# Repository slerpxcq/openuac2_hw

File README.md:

# openuac2_hw
Hardware platform for OpenUAC2 project

**WARNING**: The form factor of this module is compatible with combo384, however, the pinout is **NOT** fully the same. Check carefully before installing this card to any existing system.

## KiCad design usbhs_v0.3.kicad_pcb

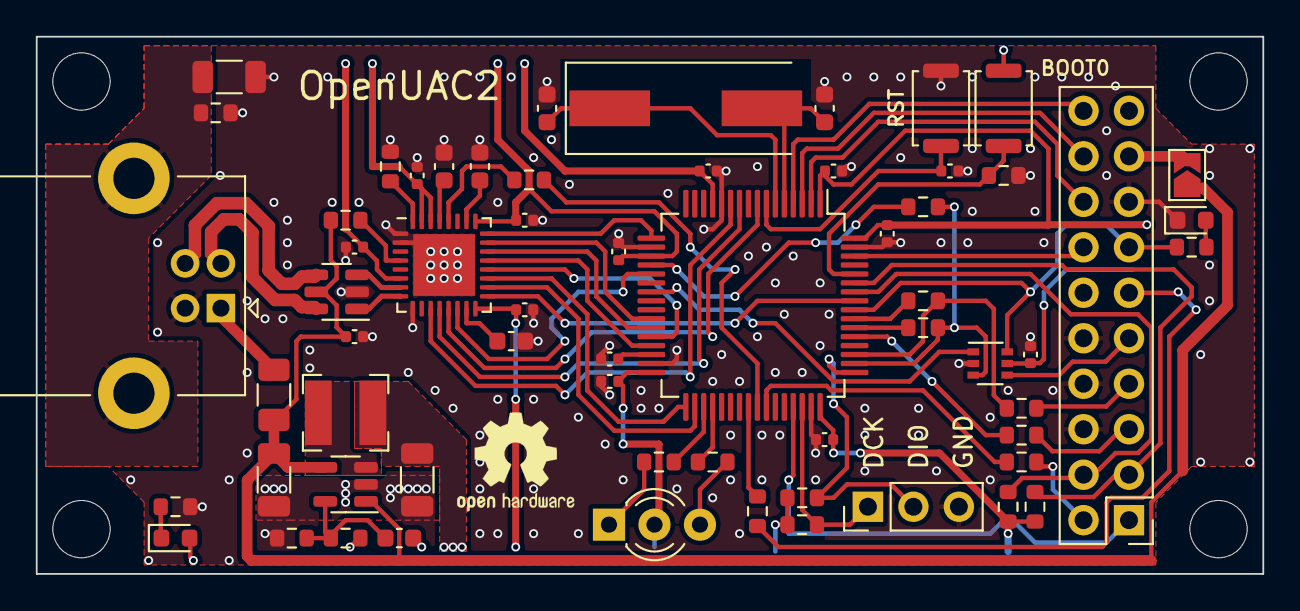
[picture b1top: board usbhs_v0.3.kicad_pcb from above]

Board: 2 copper layers, 68.5 x 30.0 mm, 66 parts (0 on the bottom side), 66 nets.

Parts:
C1, C2, C3, C4, C5, C6, C10, C12, C15, C16, C17, C18, C19, C23: 104; C_0402_1005Metric
C7, C8: 106; C_1206_3216Metric
C9: 22p; C_0603_1608Metric
C11: 104/50V; C_1206_3216Metric
C13, C14: 33p; C_0603_1608Metric
C20, C21, C22: 475; C_0603_1608Metric
D1: LED_Dual_KAK; LED_D3.0mm-3
D2: LED_WHITE; LED_0603_1608Metric
D3: LED_YELLOW; LED_0603_1608Metric
F1: 500mA; Fuse_1206_3216Metric
H1, H2, H3, H4: MountingHole; MountingHole_3.2mm_M3
J1: USB_B; USB_B_Lumberg_2411_02_Horizontal
J2: Conn_01x03; PinHeader_1x03_P2.54mm_Vertical
J3: Conn_02x10_Odd_Even; PinHeader_2x10_P2.54mm_Vertical
JP1: SolderJumper_2_Open; SolderJumper-2_P1.3mm_Open_TrianglePad1.0x1.5mm
L1: 4.7u; L_Bourns-SRN4018
R1, R2, R7, R21: 1k; R_0603_1608Metric
R3: 680k; R_0603_1608Metric
R4: 150k; R_0603_1608Metric
R5, R11, R13: 0; R_0603_1608Metric
R6: 1M; R_0603_1608Metric
R8, R9, R17: 10; R_0603_1608Metric
R10, R12, R19: 10k; R_0603_1608Metric
R14: 100k; R_0603_1608Metric
R15, R16: 4.7k; R_0603_1608Metric
R18, R20: 22; R_0603_1608Metric
R22: 12k; R_0603_1608Metric
SW1, SW2: SW_Push; SW_Push_SPST_NO_Alps_SKRK
U1: SY8088; SOT-23-5
U2: USBLC6-2SC6; SOT-23-6
U3: STM32F446RETx; LQFP-64_10x10mm_P0.5mm
U4: USB3300-EZK; QFN-32-1EP_5x5mm_P0.5mm_EP3.45x3.45mm
U5: 74LVC1G3157; SOT-363_SC-70-6
Y1: 12.288M; Crystal_SMD_HC49-SD

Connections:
+3V3: C1.2, C2.2, C3.2, C4.2, C5.2, C6.2, C7.2, C9.1, C15.1, C16.1, C17.1, C18.1, C23.1, D1.2 (A), D2.2 (A), J3.19, L1.2, R3.1, R10.1, R12.1, R15.1, R16.1, SW1.2, U3.1 (VBAT), U3.13 (VDDA), U3.19 (VDD), U3.32 (VDD), U3.48 (VDD), U3.64 (VDD), U4.6 (VDD3.3), U4.16 (VDD3.3), U4.25 (VDD3.3), U4.30 (VDD3.3), U4.31 (REG_EN), U5.5 (VCC)
/24M_CK: R8.2, U4.28 (XI)
/BOOT0: R14.2, SW1.1, U3.60 (BOOT0)
/DSDOE: J3.13, R21.2, U3.56 (PB4), U5.6
/EXTI2: R11.1, U3.54 (PD2)
/F0: J3.14, U3.62 (PB9)
/F1: J3.16, U3.2 (PC13)
/F2: J3.18, U3.3 (PC14)
/F3: J3.20, U3.4 (PC15)
/I2C1_SCL: J3.4, R15.2, U3.58 (PB6)
/I2C1_SDA: J3.3, R16.2, U3.59 (PB7)
/I2S1_CK: R13.2, U3.55 (PB3)
/I2S1_SD: U3.23 (PA7), U5.1
/I2S1_WS: R5.1, U3.20 (PA4)
/I2S3_CK: R13.1, R18.1, U3.51 (PC10)
/I2S3_SD: R20.1, U3.53 (PC12)
/I2S3_WS: R5.2, R11.2, U3.50 (PA15), U5.3
/I2S_BCK/DSDCK: J3.7, R18.2
/I2S_DATA/DSD1: J3.5, R20.2
/I2S_LRCK/DSD2: J3.9, U5.4
/I2S_MCK: J3.11, R17.2
/LED1: R1.2, U3.35 (PB14)
/LED2: R2.2, U3.36 (PB15)
/NRST: C19.1, SW2.2, U3.7 (NRST)
/PDN: J3.1, U3.45 (PA12)
/RCC_MCO1: R8.1, U3.41 (PA8)
/RCC_MCO2: R17.1, U3.40 (PC9)
/SPDIF_TX: J3.2, R9.2
/SWD_CK: J2.2, R12.2, U3.49 (PA14)
/SWD_IO: J2.1, R10.2, U3.46 (PA13)
/ULPI_CK: U3.21 (PA5), U4.14 (CLKOUT)
/ULPI_D0: U3.17 (PA3), U4.24 (DATA0)
/ULPI_D1: U3.26 (PB0), U4.23 (DATA1)
/ULPI_D2: U3.27 (PB1), U4.22 (DATA2)
/ULPI_D3: U3.29 (PB10), U4.21 (DATA3)
/ULPI_D4: U3.28 (PB2), U4.20 (DATA4)
/ULPI_D5: U3.33 (PB12), U4.19 (DATA5)
/ULPI_D6: U3.34 (PB13), U4.18 (DATA6)
/ULPI_D7: U3.57 (PB5), U4.17 (DATA7)
/ULPI_DIR: U3.10 (PC2), U4.12 (DIR)
/ULPI_NXT: U3.11 (PC3), U4.11 (NXT)
/ULPI_STP: U3.8 (PC0), U4.13 (STP)
/USB_CONN_D+: J1.3 (D+), U2.4 (I/O2)
/USB_CONN_D-: J1.2 (D-), U2.6 (I/O1)
/USB_D+: U2.3 (I/O2), U4.7 (DP)
/USB_D-: U2.1 (I/O1), U4.8 (DM)
/USB_SHIELD: C11.1, J1.5 (Shield), R6.2
GND: C1.1, C2.1, C3.1, C4.1, C5.1, C6.1, C7.1, C8.1, C10.2, C11.2, C12.1, C13.2, C14.2, C15.2, C16.2, C17.2, C18.2, C19.2, C20.1, C21.1, C22.1, C23.2, D3.1 (K), J1.4 (GND), J2.3, J3.6, J3.8, J3.10, J3.15, R4.2, R6.1, R7.1, R14.1, R22.1, SW2.1, U1.2 (GND), U2.2 (GND), U3.12 (VSSA), U3.18 (VSS), U3.31 (VSS), U3.47 (VSS), U3.63 (VSS), U4.1 (GND), U4.2 (GND), U4.9 (RESET), U4.33 (GND), U5.2 (GND)
unnamed: C9.2, R3.2, R4.1, U1.5 (FB)
unnamed: C12.2, U3.30 (VCAP_1)
unnamed: C13.1, U3.5 (PH0), Y1.2
unnamed: C14.1, U3.6 (PH1), Y1.1
unnamed: C20.2, U4.15 (VDD1.8)
unnamed: C21.2, U4.26 (VDD1.8)
unnamed: C22.2, U4.29 (VDDA1.8)
unnamed: D1.1 (K1), R1.1
unnamed: D1.3 (K2), R2.1
unnamed: D2.1 (K), R7.2
unnamed: D3.2 (A), R21.1
unnamed: F1.1, J1.1 (VBUS)
unnamed: J3.17, JP1.2 (B)
unnamed: L1.1, U1.3 (LX)
unnamed: R9.1, U3.42 (PA9)
unnamed: R19.2, U4.4 (VBUS)
unnamed: R22.2, U4.32 (RBIAS)
VBUS: C8.2, C10.1, F1.2, JP1.1 (A), R19.1, U1.1 (EN), U1.4 (IN), U2.5 (VBUS)

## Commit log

2023-09-10 new file: #auto_saved_files# new file: .gitignore new file: usbhs_v0.3.kicad_pcb new file: usbhs_v0.3.kicad_prl new file: usbhs_v0.3.kicad_pro new file: usbhs_v0.3.kicad_sch
2023-09-10 deleted: #auto_saved_files#
2023-09-10 modified: .gitignore new file: img.png modified: usbhs_v0.3.kicad_prl
2023-09-10 modified: README.md
2023-09-10 modified: .gitignore modified: usbhs_v0.3.kicad_pcb modified: usbhs_v0.3.kicad_sch new file: usbhs_v0.3.xml
2023-09-10 modified: .gitignore modified: usbhs_v0.3.kicad_pcb modified: usbhs_v0.3.kicad_sch deleted: usbhs_v0.3.xml
2023-09-11 modified: .gitignore
2023-09-13 modified: usbhs_v0.3.kicad_pcb modified: usbhs_v0.3.kicad_sch
2023-10-22 modified: img.png modified: usbhs_v0.3.kicad_pcb modified: usbhs_v0.3.kicad_prl modified: usbhs_v0.3.kicad_pro modified: usbhs_v0.3.kicad_sch new file: usbhs_v0.3.kicad_sch-bak
2023-10-22 modified: img.png
